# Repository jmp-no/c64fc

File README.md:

# c64fc
All software related to the C64FC (Commodore 64 Flash Cart)

Firmware:

Holds the source code to build and flash the firmware.

USBaspLoader 

- USB boot loader for the AVR.

c64firmware 

- firmware sourcecode.

Hardware:

Contains Hardware schematics of the C64FC card in brd/sch format.	
	
Software:

Qt64 

- QT GUI frontend to handle upload/download of c64 images.

SIDPlay 

- QT GUI frontend to handle SID playing.

cmd64 

- Command tools to upload/download/reset/set bootloader.	
libc64fc -libc64fc library. Needed for all above as dep.

C64 images/sids needs to be placed under ROMs/C64Music.

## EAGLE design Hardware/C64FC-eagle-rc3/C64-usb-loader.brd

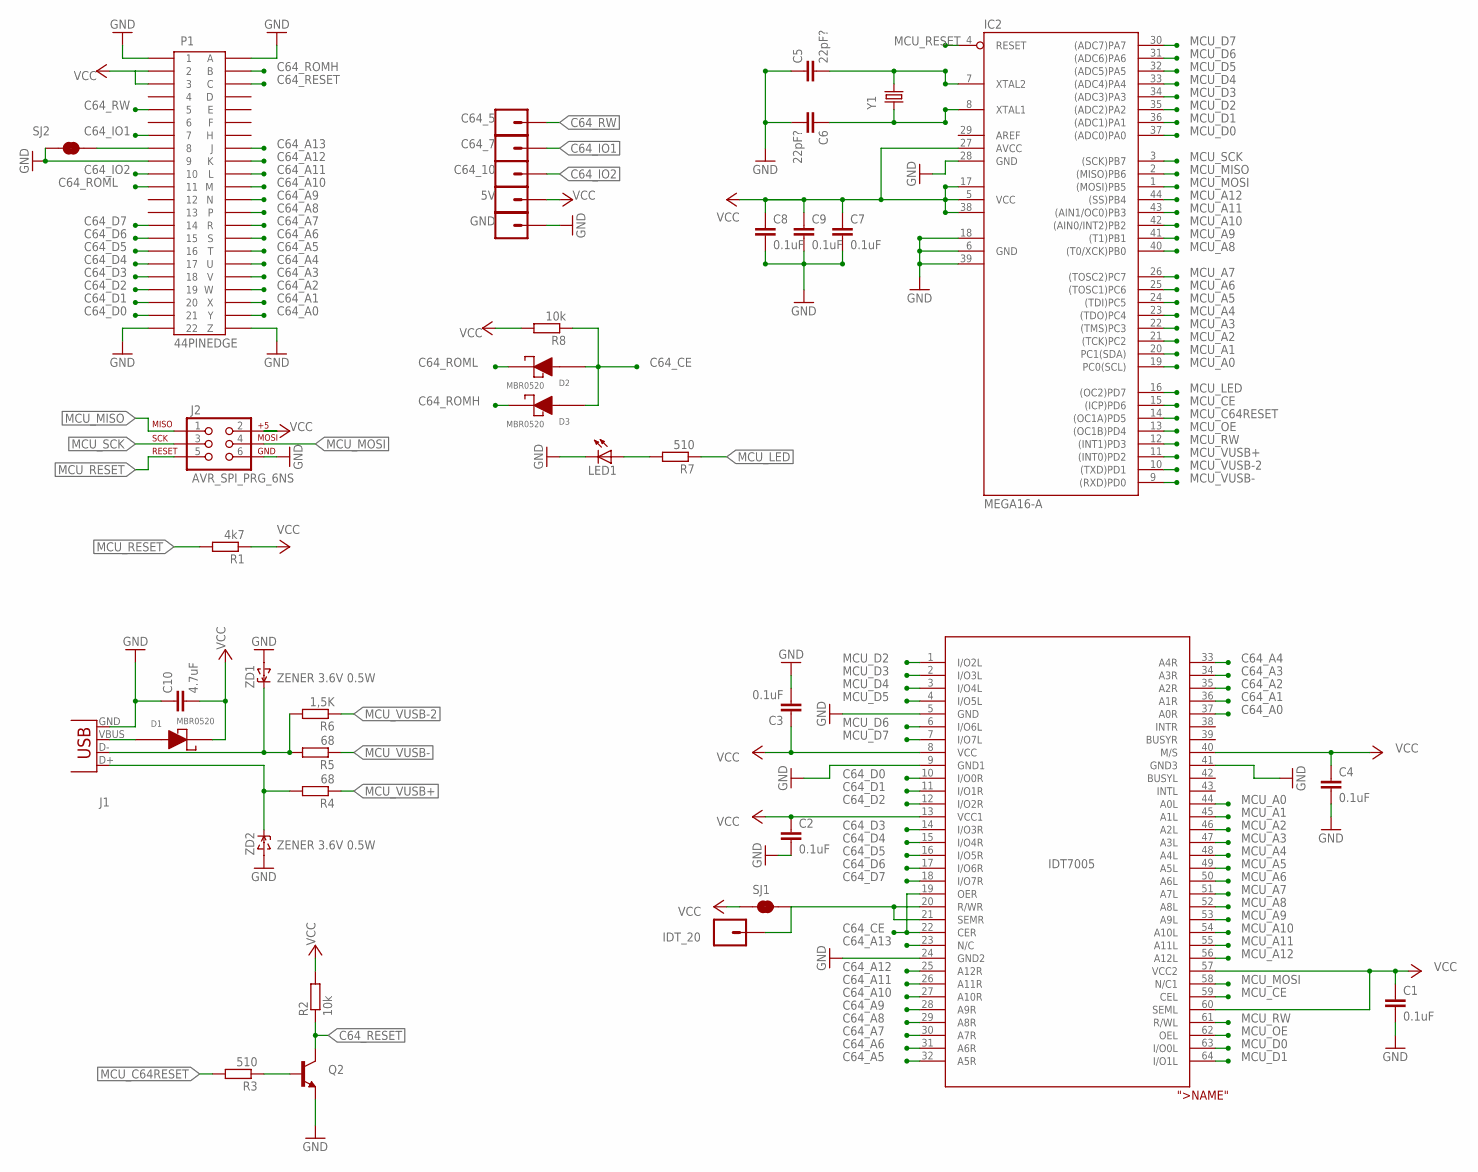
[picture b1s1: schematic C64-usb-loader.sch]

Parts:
5V: M01PTH; 1X01
C1, C2, C3, C4, C7, C8, C9: 0.1uF; C0805
C5, C6: 22pF?; C0805
C10: 4.7uF; C0805
C64_5, C64_7, C64_10: M01PTH; 1X01
D1, D2, D3: MBR0520; SOD-123; DIGIKEY MBR0520LCT-ND
GND: M01PTH; 1X01
IC1: IDT7005; TQFP64; DIGIKEY 800-1357-5-ND ??
IC2: MEGA16-A; TQFP44; DIGIKEY ATMEGA16A-AURCT-ND ??
IDT_20: M01PTH; 1X01
J1: USB-B; B; DIGIKEY ED2983-ND ??
J2: AVR_SPI_PRG_6NS; 2X3-NS
LED1: LED1206; LED-1206
P1: 44PINEDGE
Q2: TRANSISTOR_NPNSOT23-3; SOT23-3; DIGIKEY MMBT2222A-FDICT-ND
R1: 4k7; M0805
R2, R8: 10k; M0805
R3, R7: 510; M0805
R4, R5: 68; M0805
R6: 1,5K; M0805
SJ1, SJ2: JUMPER-PAD-2-NC_BY_TRACE; PAD-JUMPER-2-NC_BY_TRACE_YES_SILK
Y1: CRYSTALHC49US; HC49US
ZD1, ZD2: ZENER 3.6V 0.5W; SOD-123; DIGIKEY MMSZ5227B-FDICT-ND ??

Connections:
C64_A0: IC1.37 (A0R), P1.Y
C64_A1: IC1.36 (A1R), P1.X
C64_A2: IC1.35 (A2R), P1.W
C64_A3: IC1.34 (A3R), P1.V
C64_A4: IC1.33 (A4R), P1.U
C64_A5: IC1.32 (A5R), P1.T
C64_A6: IC1.31 (A6R), P1.S
C64_A7: IC1.30 (A7R), P1.R
C64_A8: IC1.29 (A8R), P1.P
C64_A9: IC1.28 (A9R), P1.N
C64_A10: IC1.27 (A10R), P1.M
C64_A11: IC1.26 (A11R), P1.L
C64_A12: IC1.25 (A12R), P1.K
C64_A13: IC1.23 (N/C), P1.J
C64_CE: D2.2 (AN), D3.2 (AN), IC1.19 (OER), IC1.22 (CER), R8.1
C64_D0: IC1.10 (I/O0R), P1.21
C64_D1: IC1.11 (I/O1R), P1.20
C64_D2: IC1.12 (I/O2R), P1.19
C64_D3: IC1.14 (I/O3R), P1.18
C64_D4: IC1.15 (I/O4R), P1.17
C64_D5: IC1.16 (I/O5R), P1.16
C64_D6: IC1.17 (I/O6R), P1.15
C64_D7: IC1.18 (I/O7R), P1.14
C64_GAME: P1.8, SJ2.2
C64_IO1: C64_7.1, P1.7
C64_IO2: C64_10.1, P1.10
C64_RESET: P1.C, Q2.3 (C), R2.1
C64_ROMH: D3.1 (CA), P1.B
C64_ROML: D2.1 (CA), P1.11
C64_RW: C64_5.1, P1.5
D+: J1.D+, R4.2, ZD2.C
D-: J1.D-, R5.2, R6.2, ZD1.C
GND: C1.2, C2.2, C3.2, C4.2, C5.1, C6.2, C7.2, C8.2, C9.2, C10.1, GND.1, IC1.5 (GND), IC1.9 (GND1), IC1.24 (GND2), IC1.41 (GND3), IC2.6 (GND), IC2.18 (GND1), IC2.28 (GND), IC2.39 (GND2), J1.GND, J2.6, LED1.C, P1.1, P1.9, P1.22, P1.A, P1.Z, Q2.2 (E), SJ2.1, ZD1.A, ZD2.A
MCU_A0: IC1.44 (A0L), IC2.19 (PC0(SCL))
MCU_A1: IC1.45 (A1L), IC2.20 (PC1(SDA))
MCU_A2: IC1.46 (A2L), IC2.21 ((TCK)PC2)
MCU_A3: IC1.47 (A3L), IC2.22 ((TMS)PC3)
MCU_A4: IC1.48 (A4L), IC2.23 ((TDO)PC4)
MCU_A5: IC1.49 (A5L), IC2.24 ((TDI)PC5)
MCU_A6: IC1.50 (A6L), IC2.25 ((TOSC1)PC6)
MCU_A7: IC1.51 (A7L), IC2.26 ((TOSC2)PC7)
MCU_A8: IC1.52 (A8L), IC2.40 ((T0/XCK)PB0)
MCU_A9: IC1.53 (A9L), IC2.41 ((T1)PB1)
MCU_A10: IC1.54 (A10L), IC2.42 ((AIN0/INT2)PB2)
MCU_A11: IC1.55 (A11L), IC2.43 ((AIN1/OC0)PB3)
MCU_A12: IC1.56 (A12L), IC2.44 ((SS)PB4)
MCU_C64RESET: IC2.14 ((OC1A)PD5), R3.2
MCU_CE: IC1.59 (CEL), IC2.15 ((ICP)PD6)
MCU_D0: IC1.63 (I/O0L), IC2.37 ((ADC0)PA0)
MCU_D1: IC1.64 (I/O1L), IC2.36 ((ADC1)PA1)
MCU_D2: IC1.1 (I/O2L), IC2.35 ((ADC2)PA2)
MCU_D3: IC1.2 (I/O3L), IC2.34 ((ADC3)PA3)
MCU_D4: IC1.3 (I/O4L), IC2.33 ((ADC4)PA4)
MCU_D5: IC1.4 (I/O5L), IC2.32 ((ADC5)PA5)
MCU_D6: IC1.6 (I/O6L), IC2.31 ((ADC6)PA6)
MCU_D7: IC1.7 (I/O7L), IC2.30 ((ADC7)PA7)
MCU_LED: IC2.16 ((OC2)PD7), R7.1
MCU_MISO: IC2.2 ((MISO)PB6), J2.1
MCU_MOSI: IC1.58 (N/C1), IC2.1 ((MOSI)PB5), J2.4
MCU_OE: IC1.62 (OEL), IC2.13 ((OC1B)PD4)
MCU_RESET: IC2.4 (RESET), J2.5, R1.2
MCU_RW: IC1.61 (R/WL), IC2.12 ((INT1)PD3)
MCU_SCK: IC2.3 ((SCK)PB7), J2.3
MCU_VUSB+: IC2.11 ((INT0)PD2), R4.1
MCU_VUSB-: IC2.9 ((RXD)PD0), R5.1
MCU_VUSB-2: IC2.10 ((TXD)PD1), R6.1
unnamed: Q2.1 (B), R3.1
unnamed: C5.2, IC2.7 (XTAL2), Y1.2
unnamed: IC1.20 (R/WR), IC1.21 (SEMR), IDT_20.1, SJ1.2
unnamed: C6.1, IC2.8 (XTAL1), Y1.1
unnamed: LED1.A, R7.2
VBUS: D1.2 (AN), J1.VBUS
VCC: 5V.1, C1.1, C2.1, C3.1, C4.1, C7.1, C8.1, C9.1, C10.2, D1.1 (CA), IC1.8 (VCC), IC1.13 (VCC1), IC1.40 (M/S), IC1.57 (VCC2), IC1.60 (SEML), IC2.5 (VCC), IC2.17 (VCC1), IC2.27 (AVCC), IC2.38 (VCC2), J2.2, P1.2, P1.3, R1.1, R2.2, R8.2, SJ1.1

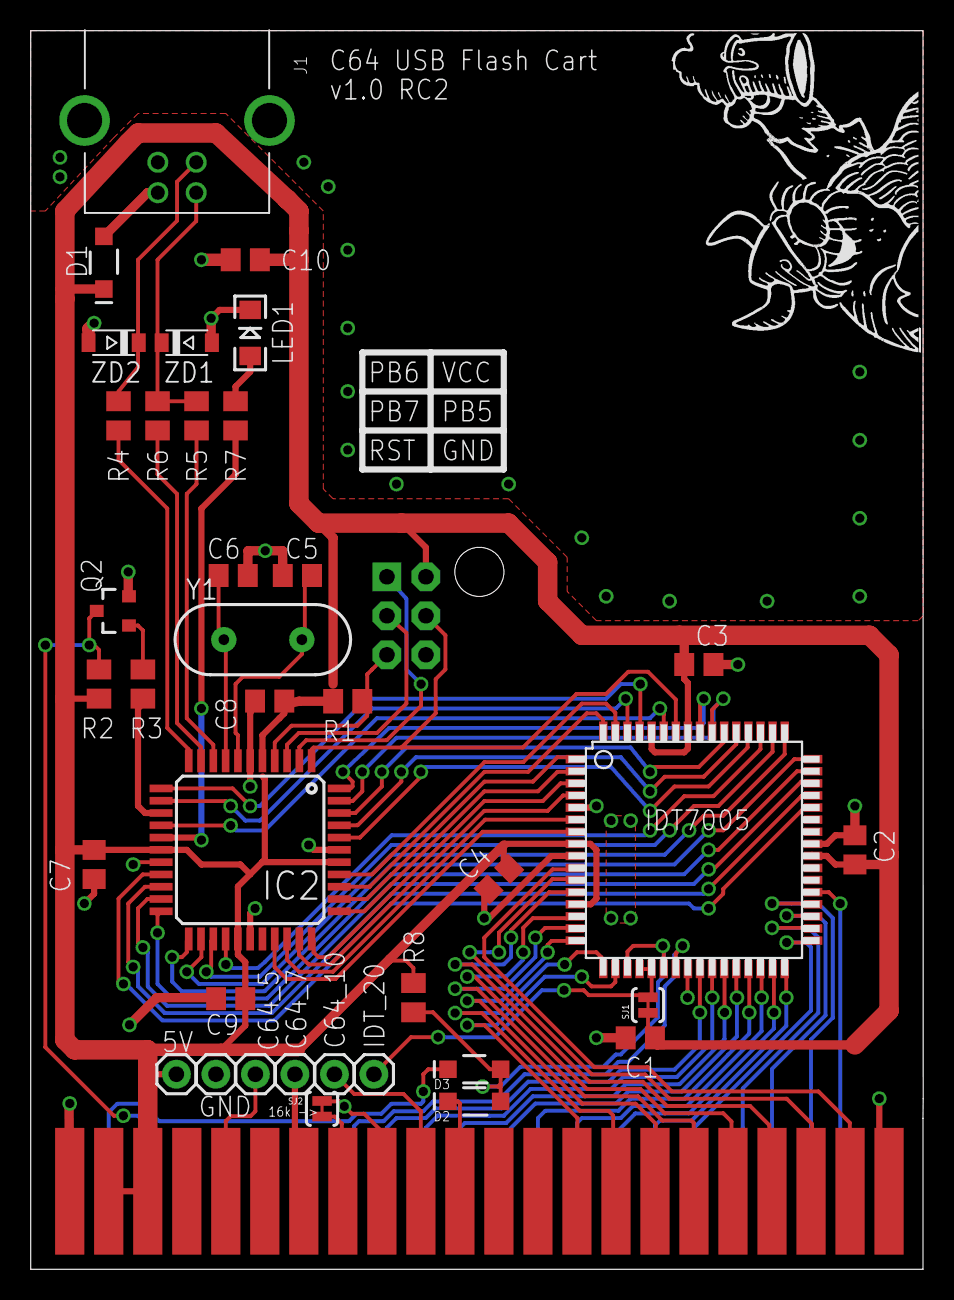
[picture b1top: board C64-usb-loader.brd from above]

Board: 2 copper layers, 58.1 x 80.6 mm, 40 parts (0 on the bottom side), 73 nets.

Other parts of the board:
U$1: HAREK_20X16MM

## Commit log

2015-04-10 Added initial .gitignore with C files
2015-04-10 Initial import of c64fc Firmware
2015-04-10 Initial import of USBaspLoader bootloader firmware
    Bootloader with modifications to fit the C64fc
2015-04-10 Initial import of lib c64fc library
2015-04-10 Initial import of software makefile and readme
2015-04-10 Initial import of CMD64
2015-04-10 Initial import of Eagle files
2015-04-10 Initial import of Qt64
2015-04-10 Initial import of SIDPlay
2015-04-10 Initial import of usbconfig.h for software
2015-04-10 Delete qt64
    axidently imported a binary executable.. :/
2015-04-10 Prettier makefile
2015-04-10 Delete cmd64
    binaries shuld not be uploaded to github.... soooorrryyy my fault.. :/
2015-04-10 Removed C64FC_EEPROM_SIZE from usbconfig.h
    This configuration was used to calculate cart rom-size, but it not used
    any more…
2015-04-10 Renamed usb name to C64FC
    size is calculated dynamically by the client, so we don’t need any
    identifier for the size any more
2015-04-10 Look for usb product
    "C64FC","C64FC-16" and "C64-08"
2015-04-10 C64 player now shows title+author of the SID tune
2015-04-10 Player now shows title+author
2015-04-11 Gitignore for cmd64
2015-04-11 Gitignore for Qt
    Updates gitignore for Qt64 and SIDPlay with Qt stuff
2015-04-11 cmd64 testfiles
    test-files for uploading to cart to check integrity..
2015-04-11 Uploaded .gitignore for SIDPlay/C64Music
    ignores .sid files
2015-04-11 Deleted moc_GUI.cpp and ui_SIDPLAY.h
    These files are created by make
2015-04-11 Updated global Software Makefile
    Makes all software running qmake and everything :)
2015-04-11 replaced ; with &&
2015-04-11 When makefile is deleted make clean failes
    fixed by ignoring error code on make commands used by make clean.
    Make clean no longer fails when makefile is not existing in SIDlay and
    Qt64
2015-04-11 Update README.md
    Made simple draft for structure that describe the rep sub.
2015-04-11 Update README.md
    tab ?
2015-04-11 Update README.md
    Now then. Using web as text editor might be an bad idea. I go fetch the ssh key and do it cmd style.
2015-04-12 Update README.md
    Draft readme..
2015-04-12 Update README.md
    Looks better with - style ?
2015-04-12 Some improvements
2015-04-17 IDea
2015-04-19 Git ignore files for AVR projects
2015-04-19 Set Mode
    Function to Set GAME and EXROM status on the C64. sets all 4 modes in
    the same function, and does not reboot the C64 when changing mode
2015-04-19 Get API Version
    function that returns the usb hid api version running on the cart, the
    result of this function should be incremented every time there are
    changed in usb hid functions that would brick older implementations..

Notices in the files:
parts and their libraries:
SparkFun-DiscreteSemi: Licensing: CC v3.0 Share-Alike You are welcome to use this library for commercial purposes.
SparkFun-Passives: Licensing: Creative Commons ShareAlike 4.0 International - https://creativecommons.org/licenses/by-sa/4.0
